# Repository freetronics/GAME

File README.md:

Freetronics Game Controller Shield
==================================
Copyright 2015 Freetronics Pty Ltd  
Freetronics site:  www.freetronics.com  
Freetronics email: info@freetronics.com  

A shield for the Arduino and other microcontroller boards based on the
same header format, such as the Freetronics Eleven. Include a joystick,
buttons, a header for a Freetronics 128x128 Pixel OLED Module, and
a prototyping area.

Safe operation on both 3.3V and 5V Arduino boards.

More information is available on our product page at:

  http://tron.cc/game

INSTALLATION
------------
The design is saved as an EAGLE project. EAGLE PCB design software is
available from www.cadsoftusa.com free for non-commercial use. To use
this project download it and place the directory containing these files
into the "eagle" directory on your computer. Then open EAGLE and
navigate to Projects -> eagle -> GAME.

DISTRIBUTION
------------
The specific terms of distribution of this project are governed by the
license referenced below.

LICENSE
-------
Licensed under the TAPR Open Hardware License (www.tapr.org/OHL).
The "license" folder within this repository also contains a copy of
this license in plain text format.

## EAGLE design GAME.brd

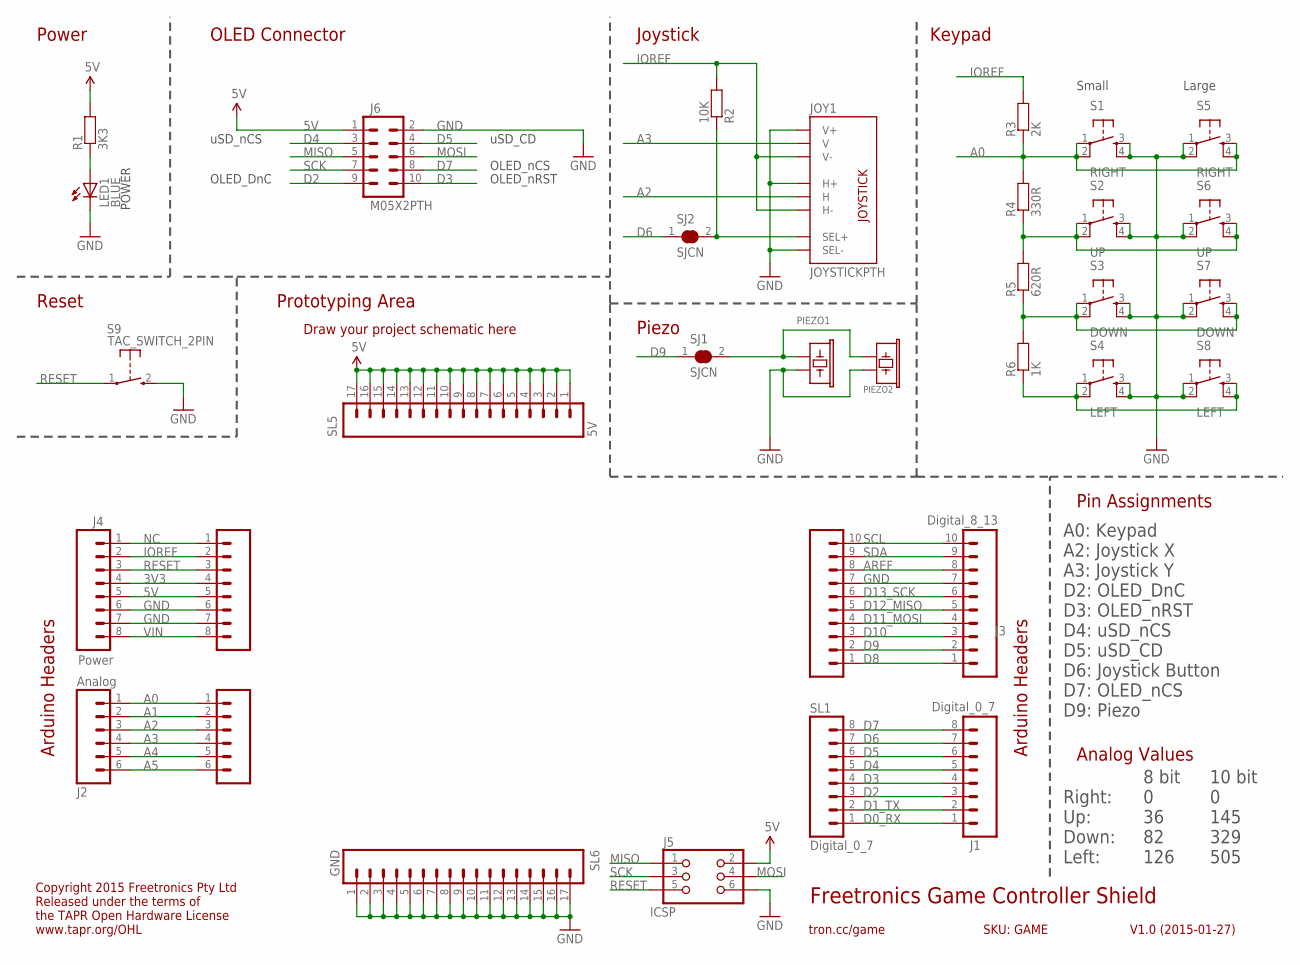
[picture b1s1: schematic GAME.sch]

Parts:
J1: Digital_0_7; 1X08
J2: Analog; 1X06
J3: Digital_8_13; 1X10
J4: Power; 1X08
J5: ICSP; 2X03PTH
J6: M05X2PTH; AVR_ICSP
JOY1: JOYSTICKPTH; JOYSTICK
LED1: BLUE; LED-0603
PIEZO1: BUZZERSMD12X12; BUZZER-12X12-SMT
PIEZO2: PIEZO12MM
R1: 3K3; 0603
R2: 10K; 0603
R3: 2K; 0603
R4: 330R; 0603
R5: 620R; 0603
R6: 1K; 0603
S1: RIGHT; TACTILE-PTH
S2: UP; TACTILE-PTH
S3: DOWN; TACTILE-PTH
S4: LEFT; TACTILE-PTH
S5: RIGHT; TACTILE-PTH-12MM
S6: UP; TACTILE-PTH-12MM
S7: DOWN; TACTILE-PTH-12MM
S8: LEFT; TACTILE-PTH-12MM
S9: TAC_SWITCH_2PIN; TACTILE_SWITCH_SMD_2PIN_TINY
SJ1, SJ2: SJCN; SJC
SL1: Digital_0_7; 1X08
SL2: Analog; 1X06
SL3: Digital_8_13; 1X10
SL4: Power; 1X08
SL5: 5V; 1X17
SL6: GND; 1X17

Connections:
3V3: J4.4, SL4.4
5V: J4.5, J5.2, J6.1, R1.2, SL4.5, SL5.1, SL5.2, SL5.3, SL5.4, SL5.5, SL5.6, SL5.7, SL5.8, SL5.9, SL5.10, SL5.11, SL5.12, SL5.13, SL5.14, SL5.15, SL5.16, SL5.17
A0: J2.1, R3.1, R4.2, S1.1, S1.2, S5.3, S5.4, SL2.1
A1: J2.2, SL2.2
A2: J2.3, JOY1.H2 (H), SL2.3
A3: J2.4, JOY1.V2 (V), SL2.4
A4: J2.5, SL2.5
A5: J2.6, SL2.6
AREF: J3.8, SL3.8
D0_RX: J1.1, SL1.1
D1_TX: J1.2, SL1.2
D2: J1.3, J6.9, SL1.3
D3: J1.4, J6.10, SL1.4
D4: J1.5, J6.3, SL1.5
D5: J1.6, J6.4, SL1.6
D6: J1.7, SJ2.1, SL1.7
D7: J1.8, J6.8, SL1.8
D8: J3.1, SL3.1
D9: J3.2, SJ1.1, SL3.2
D10: J3.3, SL3.3
D11_MOSI: J3.4, SL3.4
D12_MISO: J3.5, SL3.5
D13_SCK: J3.6, SL3.6
GND: J3.7, J4.6, J4.7, J5.6, J6.2, JOY1.B2A (SEL-), JOY1.H1 (H+), JOY1.V1 (V+), LED1.C, PIEZO1.1, PIEZO2.2, S1.3, S1.4, S2.3, S2.4, S3.3, S3.4, S4.3, S4.4, S5.1, S5.2, S6.1, S6.2, S7.1, S7.2, S8.1, S8.2, S9.2 (S), SL3.7, SL4.6, SL4.7, SL6.1, SL6.2, SL6.3, SL6.4, SL6.5, SL6.6, SL6.7, SL6.8, SL6.9, SL6.10, SL6.11, SL6.12, SL6.13, SL6.14, SL6.15, SL6.16, SL6.17
IOREF: J4.2, JOY1.H3 (H-), JOY1.V3 (V-), R2.2, R3.2, SL4.2
MISO: J5.1, J6.5
MOSI: J5.4, J6.6
unnamed: LED1.A, R1.1
unnamed: PIEZO1.2, PIEZO2.1, SJ1.2
unnamed: JOY1.B1A (SEL+), R2.1, SJ2.2
unnamed: R6.1, S4.1, S4.2, S8.3, S8.4
unnamed: R5.1, R6.2, S3.1, S3.2, S7.3, S7.4
unnamed: R4.1, R5.2, S2.1, S2.2, S6.3, S6.4
NC: J4.1, SL4.1
RESET: J4.3, J5.5, S9.1, SL4.3
SCK: J5.3, J6.7
SCL: J3.10, SL3.10
SDA: J3.9, SL3.9
VIN: J4.8, SL4.8

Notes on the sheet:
Freetronics Game Controller Shield
V1.0 (2015-01-27)
tron.cc/game
SKU: GAME
Arduino Headers
Draw your project schematic here
Copyright 2015 Freetronics Pty Ltd Released under the terms of the TAPR Open Hardware License www.tapr.org/OHL
POWER
OLED_DnC
uSD_CD
OLED_nCS
OLED_nRST
uSD_nCS
Keypad
Joystick
OLED Connector
A0: Keypad A2: Joystick X A3: Joystick Y D2: OLED_DnC D3: OLED_nRST D4: uSD_nCS D5: uSD_CD D6: Joystick Button D7: OLED_nCS D9: Piezo
Power
Reset
Piezo
Prototyping Area
Pin Assignments
10 bit 0 145 329 505
8 bit 0 36 82 126
Right: Up: Down: Left:
Analog Values
Small
Large

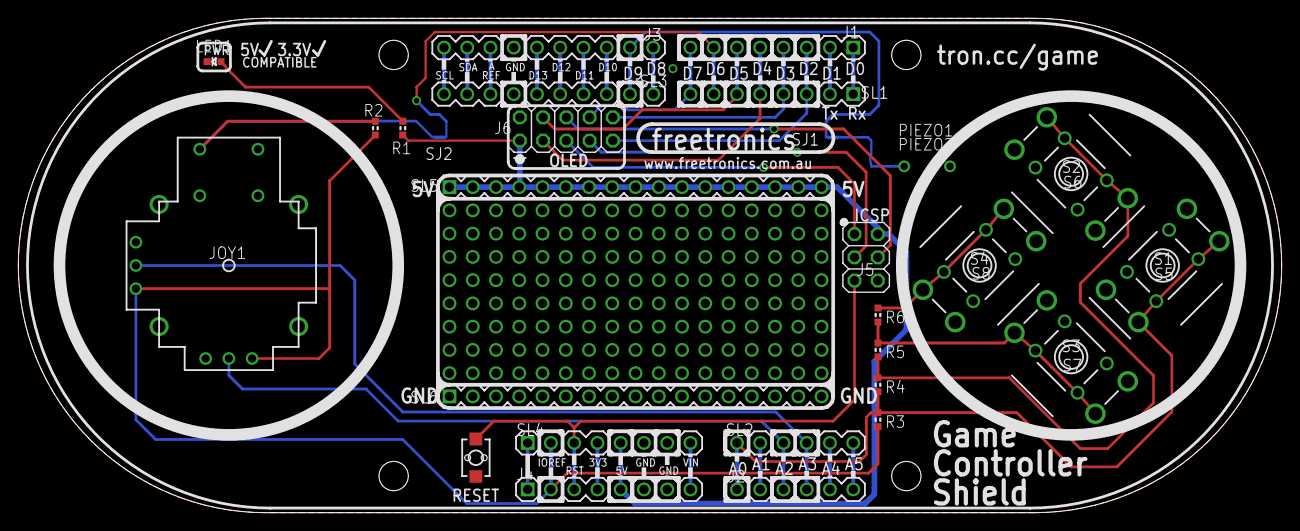
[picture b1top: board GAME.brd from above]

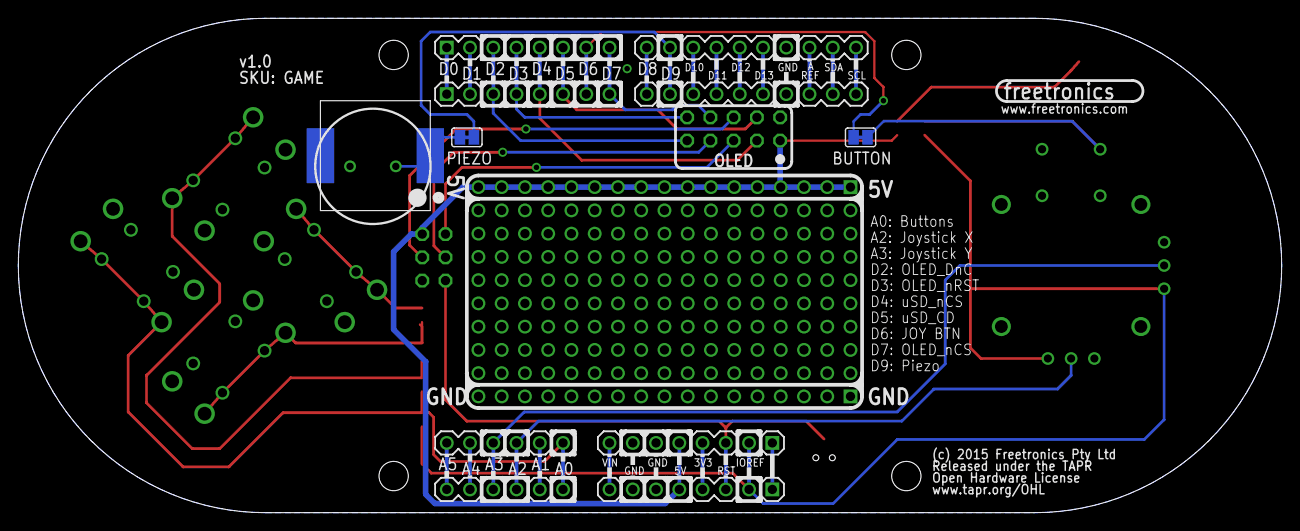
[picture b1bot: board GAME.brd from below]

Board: 2 copper layers, 138.0 x 54.0 mm, 33 parts (4 on the bottom side), 39 nets.

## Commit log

2015-02-09 Initial project import for v1.0 release
2019-04-24 Fixed OLED pinout for v1.1 release

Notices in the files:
GAME.brd:
(c) 2015 Freetronics Pty Ltd
Open Hardware License
